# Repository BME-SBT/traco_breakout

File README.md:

# README
I've used some symbols/footprints for the PCB which I downloaded mostly from SamacSys and SnapEDA. If you have issues with KiCad not finding certain footprints/symbols, look for them in the "includes" folder.

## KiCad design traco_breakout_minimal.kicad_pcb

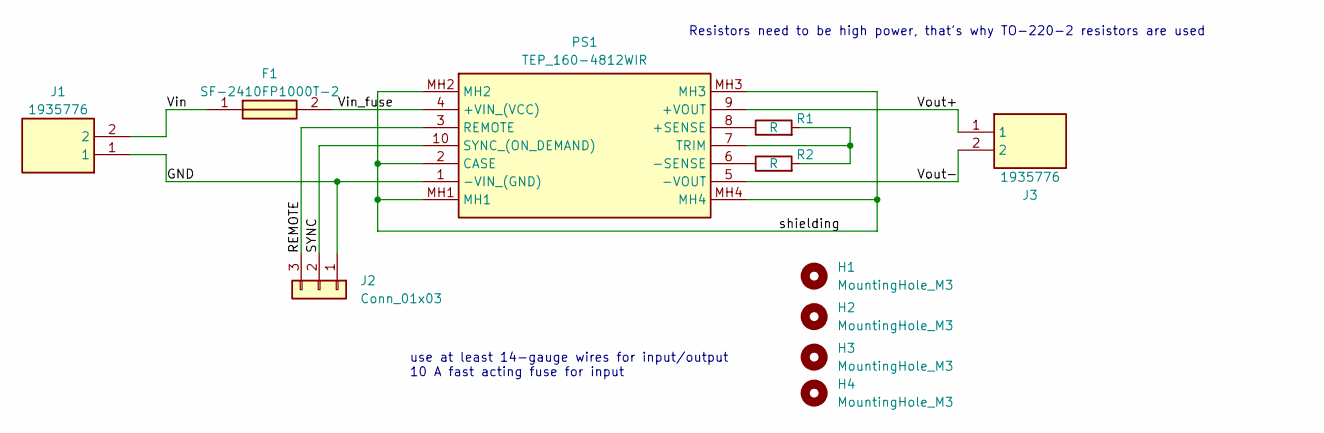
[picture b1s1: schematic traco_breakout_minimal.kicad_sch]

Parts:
F1: SF-2410FP1000T-2; FUSC6126X270N; Manufacturer_Part_Number SF-2410FP1000T-2; Mouser Part Number 652-SF-2410FP1000T-2
H1, H2, H3, H4: MountingHole_M3; MountingHole_3.2mm_M3
J1, J3: 1935776; Manufacturer_Part_Number 1935776; Mouser Part Number 651-1935776
J2: Conn_01x03; PinHeader_1x03_P2.54mm_Vertical
PS1: TEP_160-4812WIR; TEP1602415WIR; Manufacturer_Part_Number TEP 160-4812WIR; Mouser Part Number 495-TEP160-4812WIR
R1, R2: R; TO-220-2_Vertical

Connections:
/GND: J1.1, J2.1, PS1.1 (-VIN_(GND))
/REMOTE: J2.3, PS1.3 (REMOTE)
/SYNC: J2.2, PS1.10 (SYNC_(ON_DEMAND))
/Vin: F1.1, J1.2
/Vin_fuse: F1.2, PS1.4 (+VIN_(VCC))
/Vout+: J3.1, PS1.9 (+VOUT)
/Vout-: J3.2, PS1.5 (-VOUT)
/shielding: PS1.2 (CASE), PS1.MH1, PS1.MH2, PS1.MH3, PS1.MH4
unnamed: PS1.8 (+SENSE), R1.1
unnamed: PS1.6 (-SENSE), R2.1
unnamed: PS1.7 (TRIM), R1.2, R2.2

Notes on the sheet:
use at least 14-gauge wires for input/output 10 A fast acting fuse for input
Resistors need to be high power, that's why TO-220-2 resistors are used

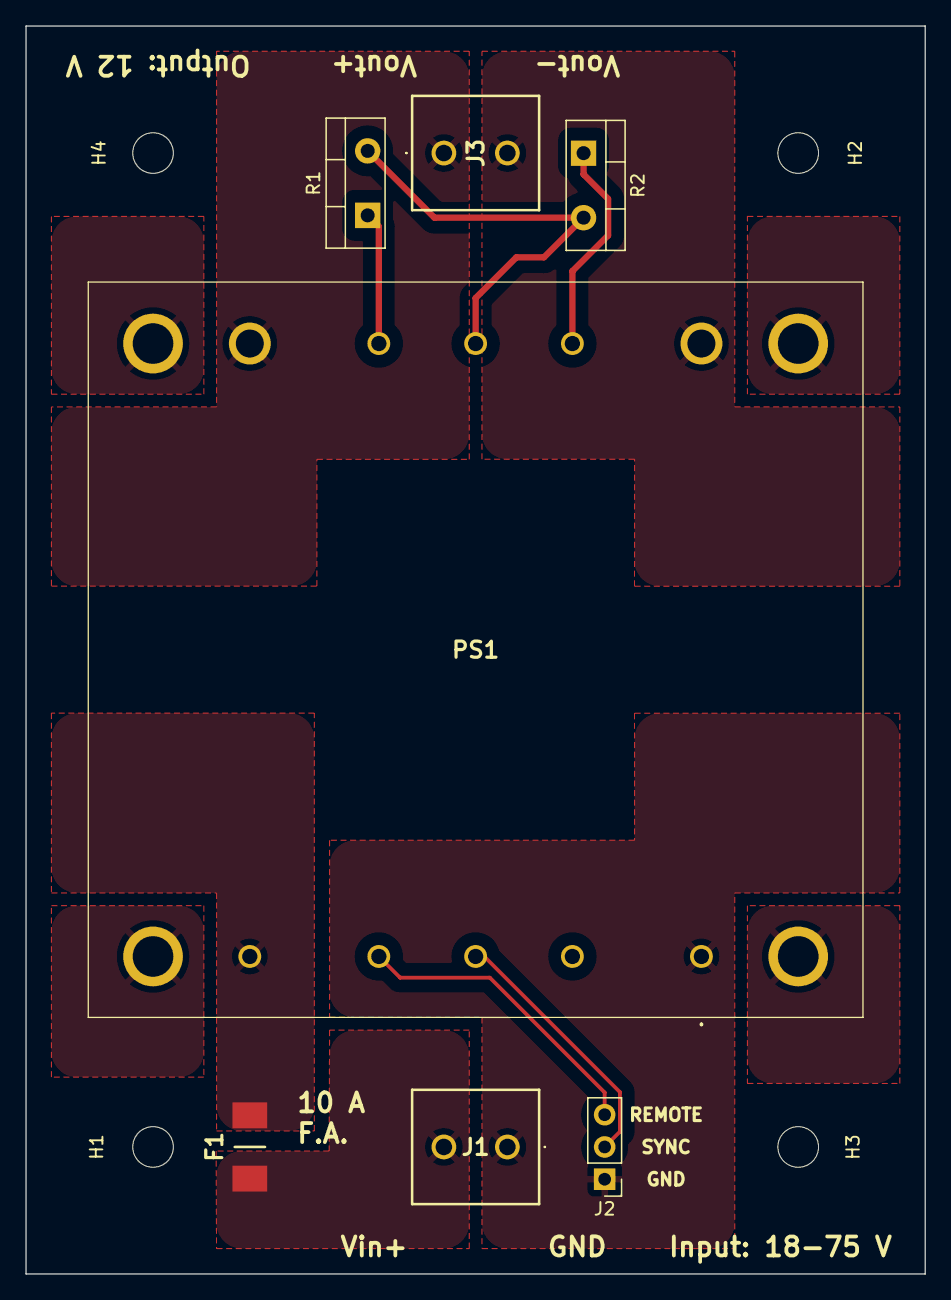
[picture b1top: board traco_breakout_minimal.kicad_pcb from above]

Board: 2 copper layers, 70.8 x 98.3 mm, 11 parts (0 on the bottom side), 11 nets.

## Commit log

2023-04-15 Initial version of traco breakout
2023-04-23 before potentiometer branch
2023-05-04 Gerbers generated.
